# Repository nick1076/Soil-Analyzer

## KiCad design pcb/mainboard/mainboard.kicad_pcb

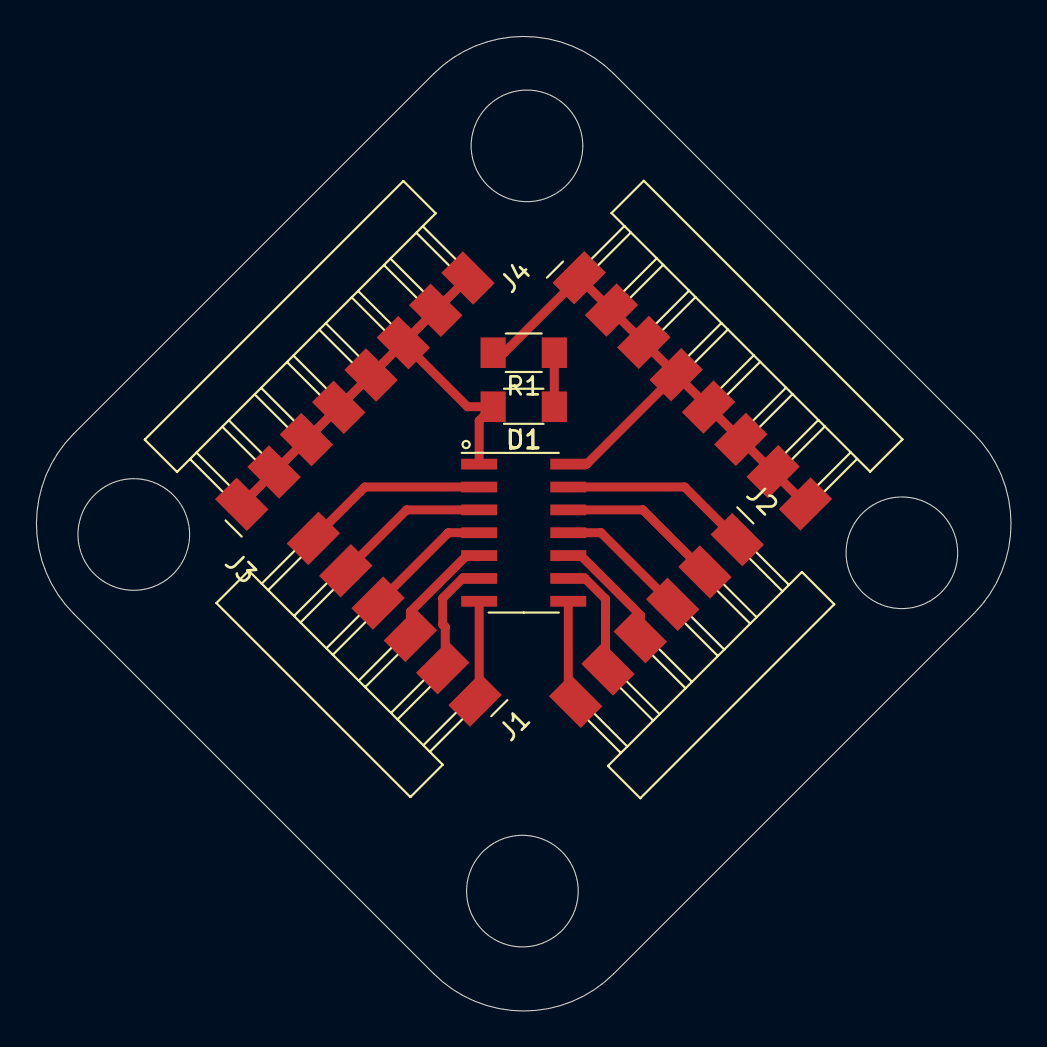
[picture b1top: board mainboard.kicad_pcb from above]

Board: 2 copper layers, 54.1 x 54.1 mm, 7 parts (0 on the bottom side), 15 nets.

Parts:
D1: LED_1206
J1, J2: Conn_PinHeader_1x06_P2.54mm_Horizontal_SMD; PinHeader_1x06_P2.54mm_Horizontal_SMD
J3, J4: Conn_PinHeader_1x08_P2.54mm_Horizontal_SMD; PinHeader_1x08_P2.54mm_Horizontal_SMD
R1: R_1206
U1: Microcontroller_ATtiny1614-SSFR; SOIC-14_3.9x8.7mm_P1.27mm

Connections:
unnamed: D1.2 (A), J3.1, J3.2, J3.3, J3.4, J3.5, J3.6, J3.7, J3.8, U1.1 (VCC)
unnamed: D1.1 (K), R1.1
unnamed: J1.1, U1.7 (PB2/TXD)
unnamed: J1.2, U1.6 (PB3/RXD)
unnamed: J1.3, U1.5 (PA7)
unnamed: J1.4, U1.4 (PA6/DAC)
unnamed: J1.5, U1.3 (PA5)
unnamed: J1.6, U1.2 (PA4)
unnamed: J2.1, U1.13 (PA3/SCK)
unnamed: J2.2, U1.12 (PA2)
unnamed: J2.3, U1.11 (PA1)
unnamed: J2.4, U1.10 (~RESET/UPDI/PA0)
unnamed: J2.5, U1.9 (PB0/SCL)
unnamed: J2.6, U1.8 (PB1/SDA)
unnamed: J4.1, J4.2, J4.3, J4.4, J4.5, J4.6, J4.7, J4.8, R1.2, U1.14 (GND)

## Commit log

2024-04-12 v1.0 - Links For Prototype 1
    Implemented file containing links to research and tutorials needed to complete Prototype 1 of the project.
2024-04-12 v1.1 - Added Schematics & Sample Code
    Added a folder for research specifically and added schematics and code that I found for the project via my research into this folder.
2024-04-13 v1.2 - Began Unity Project
    Began Unity project and imported needed packages.
2024-04-13 v1.3 - Missing File Addition
2024-04-16 v1.4 - Cleaning Up
2024-04-16 v1.5 - Unity Serial Updates
2024-04-22 arduino
2024-04-22 v1.7 - Combined Code Implimentation
2024-04-23 v1.8 - Upgraded Unity Graphics
2024-04-23 v1.9 - PCB Addition
2024-06-03 Huge UI Updates
